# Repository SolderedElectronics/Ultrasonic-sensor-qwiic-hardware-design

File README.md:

# Ultrasonic sensor qwiic Hardware Design

## About the Product

|  |
| :----------------------------------------------------------: |
| [Buy Ultrasonic sensor qwiic](https://www.solde.red/333001) |

The HC-SR04 ultrasonic sensor is an affordable and super-popular sensor that measures the distance between itself and an object located in front of the sensor. Very simple to use, it returns the distance in centimeters or inches.
In this variation, it comes on a board with an Attiny microcontroller that sends readings from the sensor as a digital signal via the qwiic connector to the microcontroller, which makes its connections a piece of cake.

---

## Repository Contents

This repository contains all design files for Ultrasonic sensor qwiic, organized as follows:

- **`CAD` folder**: Contains KiCAD design files, including:
  - Schematics
  - PCB layout
  - Panel PCB layout
  - Source 3D files in Fusion360, if any
  - All files are sorted by version with a detailed change log.
- **`OUTPUTS` folder**: Includes all production-ready files, such as:
  - Bill of Materials (BOM) and interactive BOM (iBOM)
  - PDF versions of schematics
  - 3D `.step` file of the board
  - 3D-printable models
  - Gerber files for PCB manufacturing
  - Image of the pinout of the board
  - Product image
  - Compliance, legal and generic sales documents

Refer to the `Change Log` in the CAD folder for details about updates between versions.

---

## Learn More About the Product

Beyond the repository, explore the following resources:

### Soldered Verify

The **Soldered Verify** system ensures every board you purchase from Soldered is fully functional. It also provides access to exclusive test data for your product. To get started, find the unique Soldered Verify ID on your product's packaging and enter the ID on the [Soldered Verify page](https://soldered.com/verify/) to access test results and additional product details.

### Soldered Community

Soldered Community is your go-to place for technical support. Our engineers track and answer all questions posted there, and it’s a great space for the maker community. Get answers to your questions and solutions for your challenges at [Soldered Community](https://soldered.com/community).

### solde.red

solde.red is an ultimate URL shortener and information hub. Access it by typing solde.red/ followed by your product SKU, e.g., [solde.red/333000](https://solde.red/333000), to find getting-started guides, datasheets, open-source hardware and software files, certifications, images, pinouts, and more. Read more about the shortener [here](https://solde.red/info/).

---

## Contributing

Contributions are welcome! Here’s how you can get involved:

- Submit pull requests to enhance the design or fix issues.
- Report bugs or problems by opening an issue.

We encourage community collaboration to make this product even better.

---

## About Soldered

[Soldered for Makers](https://soldered.com) specializes in designing and manufacturing electronic products tailored for enthusiasts, ranging from hobbyists to professionals. Our portfolio includes electronic boards, sensors, and actuators that are widely utilized in fields such as microelectronics, mechatronics, robotics, programming, and IoT. Every product we offer is designed in-house and built upon open-source hardware and software platforms. Proudly certified and manufactured within the European Union, our catalog likely includes the product you need for your project.

We complement these products with comprehensive tutorials and manuals, product descriptions, schematics, programming codes, and project examples. Our round-the-clock [customer and technical support](https://soldered.com/community) is available for all our products, irrespective of the sales channel. Soldered’s success and services reflect our maker community’s unwavering [trust](https://www.trustpilot.com/review/soldered.com), for which we are deeply grateful. Join our community and create using Soldered products.

---

## License

All Soldered open-source hardware (OSH) is under The TAPR Open Hardware License. Read more in the LICENSE file located in this repository.

**Disclaimer:**

No warranty - all designs in this repository are distributed in the hope that they will be useful, but without any warranty. They are provided "AS IS", therefore without warranty of any kind, either expressed or implied. The entire quality and performance of what you do with the contents of this repository are your responsibility. In no event Soldered Electronics will be liable for your damages, or losses, including any general, special, incidental, or consequential damage arising out of the use or inability to use the contents of this repository. 

---

## Have fun!

Thank you for your support from your fellow makers at Soldered Electronics.

Happy Making!

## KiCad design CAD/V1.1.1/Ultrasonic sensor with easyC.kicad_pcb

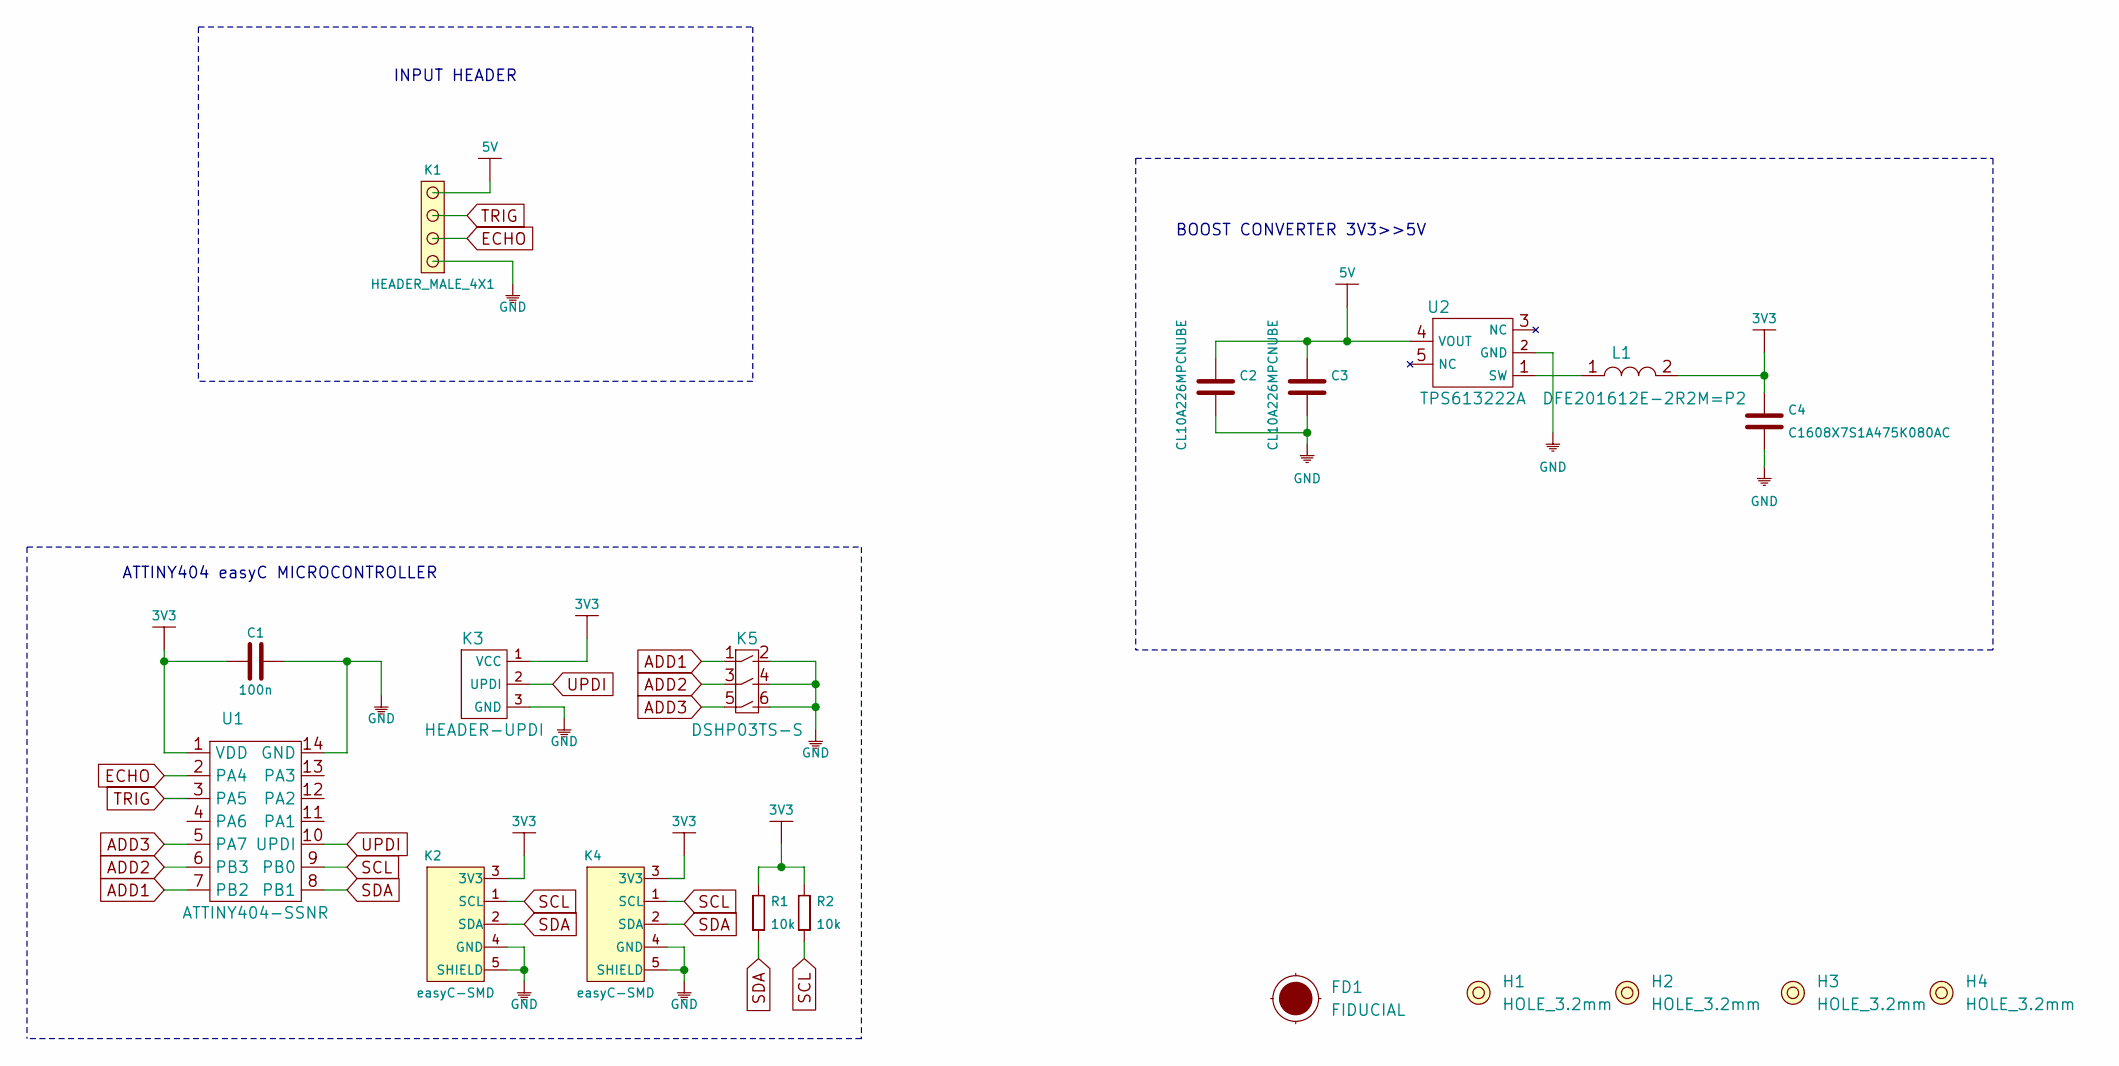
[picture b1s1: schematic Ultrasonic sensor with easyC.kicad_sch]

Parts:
C1: 100n; 0603C
C2, C3: CL10A226MPCNUBE; 0805C
C4: C1608X7S1A475K080AC; 0805C
FD1: FIDUCIAL; FIDUCIAL_23
H1, H2, H3, H4: HOLE_3.2mm
K1: HEADER_MALE_4X1
K2, K4: easyC-SMD; easyC-connector
K3: HEADER-UPDI
K5: DSHP03TS-S
L1: DFE201612E-2R2M=P2; 0806L
R1, R2: 10k; 0603R
U1: ATTINY404-SSNR; SOIC-14
U2: TPS613222A; tps613222a

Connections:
3V3: C1.1, C4.2, K2.3 (3V3), K3.1 (VCC), K4.3 (3V3), L1.2, R1.2, R2.2, U1.1 (VDD)
5V: C2.2, C3.2, K1.4, U2.4 (VOUT)
ADD1: K5.1, U1.7 (PB2)
ADD2: K5.3, U1.6 (PB3)
ADD3: K5.5, U1.5 (PA7)
ECHO: K1.2, U1.2 (PA4)
GND: C1.2, C2.1, C3.1, C4.1, K1.1, K2.4 (GND), K2.5 (SHIELD), K3.3 (GND), K4.4 (GND), K4.5 (SHIELD), K5.2, K5.4, K5.6, U1.14 (GND), U2.2 (GND)
unnamed: L1.1, U2.1 (SW)
SCL: K2.1 (SCL), K4.1 (SCL), R2.1, U1.9 (PB0)
SDA: K2.2 (SDA), K4.2 (SDA), R1.1, U1.8 (PB1)
TRIG: K1.3, U1.3 (PA5)
UPDI: K3.2 (UPDI), U1.10 (UPDI)

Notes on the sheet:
BOOST CONVERTER 3V3>>5V
ATTINY404 easyC MICROCONTROLLER
INPUT HEADER

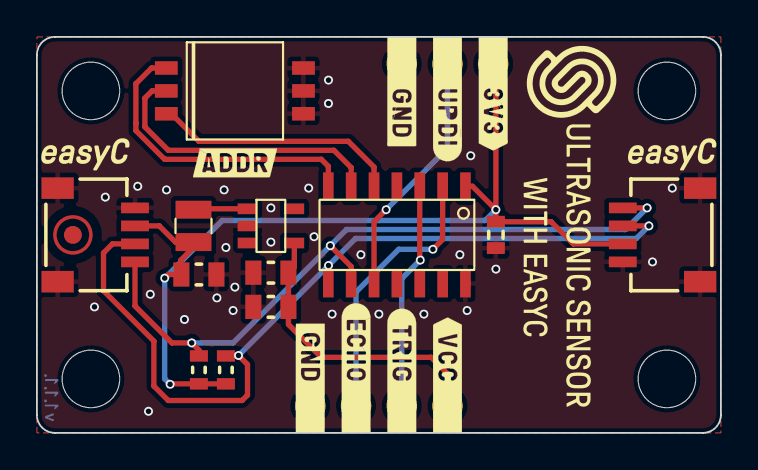
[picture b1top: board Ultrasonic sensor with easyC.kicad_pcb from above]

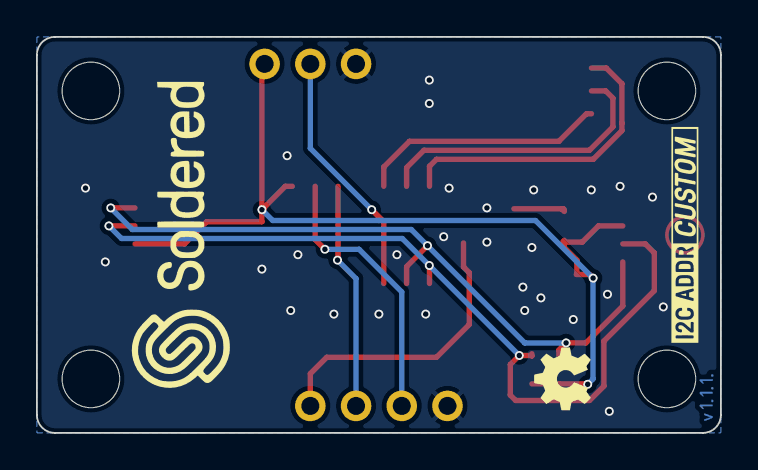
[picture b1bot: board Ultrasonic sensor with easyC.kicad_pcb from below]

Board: 2 copper layers, 38.0 x 22.0 mm, 20 parts (2 on the bottom side), 12 nets.

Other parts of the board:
kibuzzard-62454551: G***; kibuzzard-62454551

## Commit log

2022-08-06 Updating open source files.
